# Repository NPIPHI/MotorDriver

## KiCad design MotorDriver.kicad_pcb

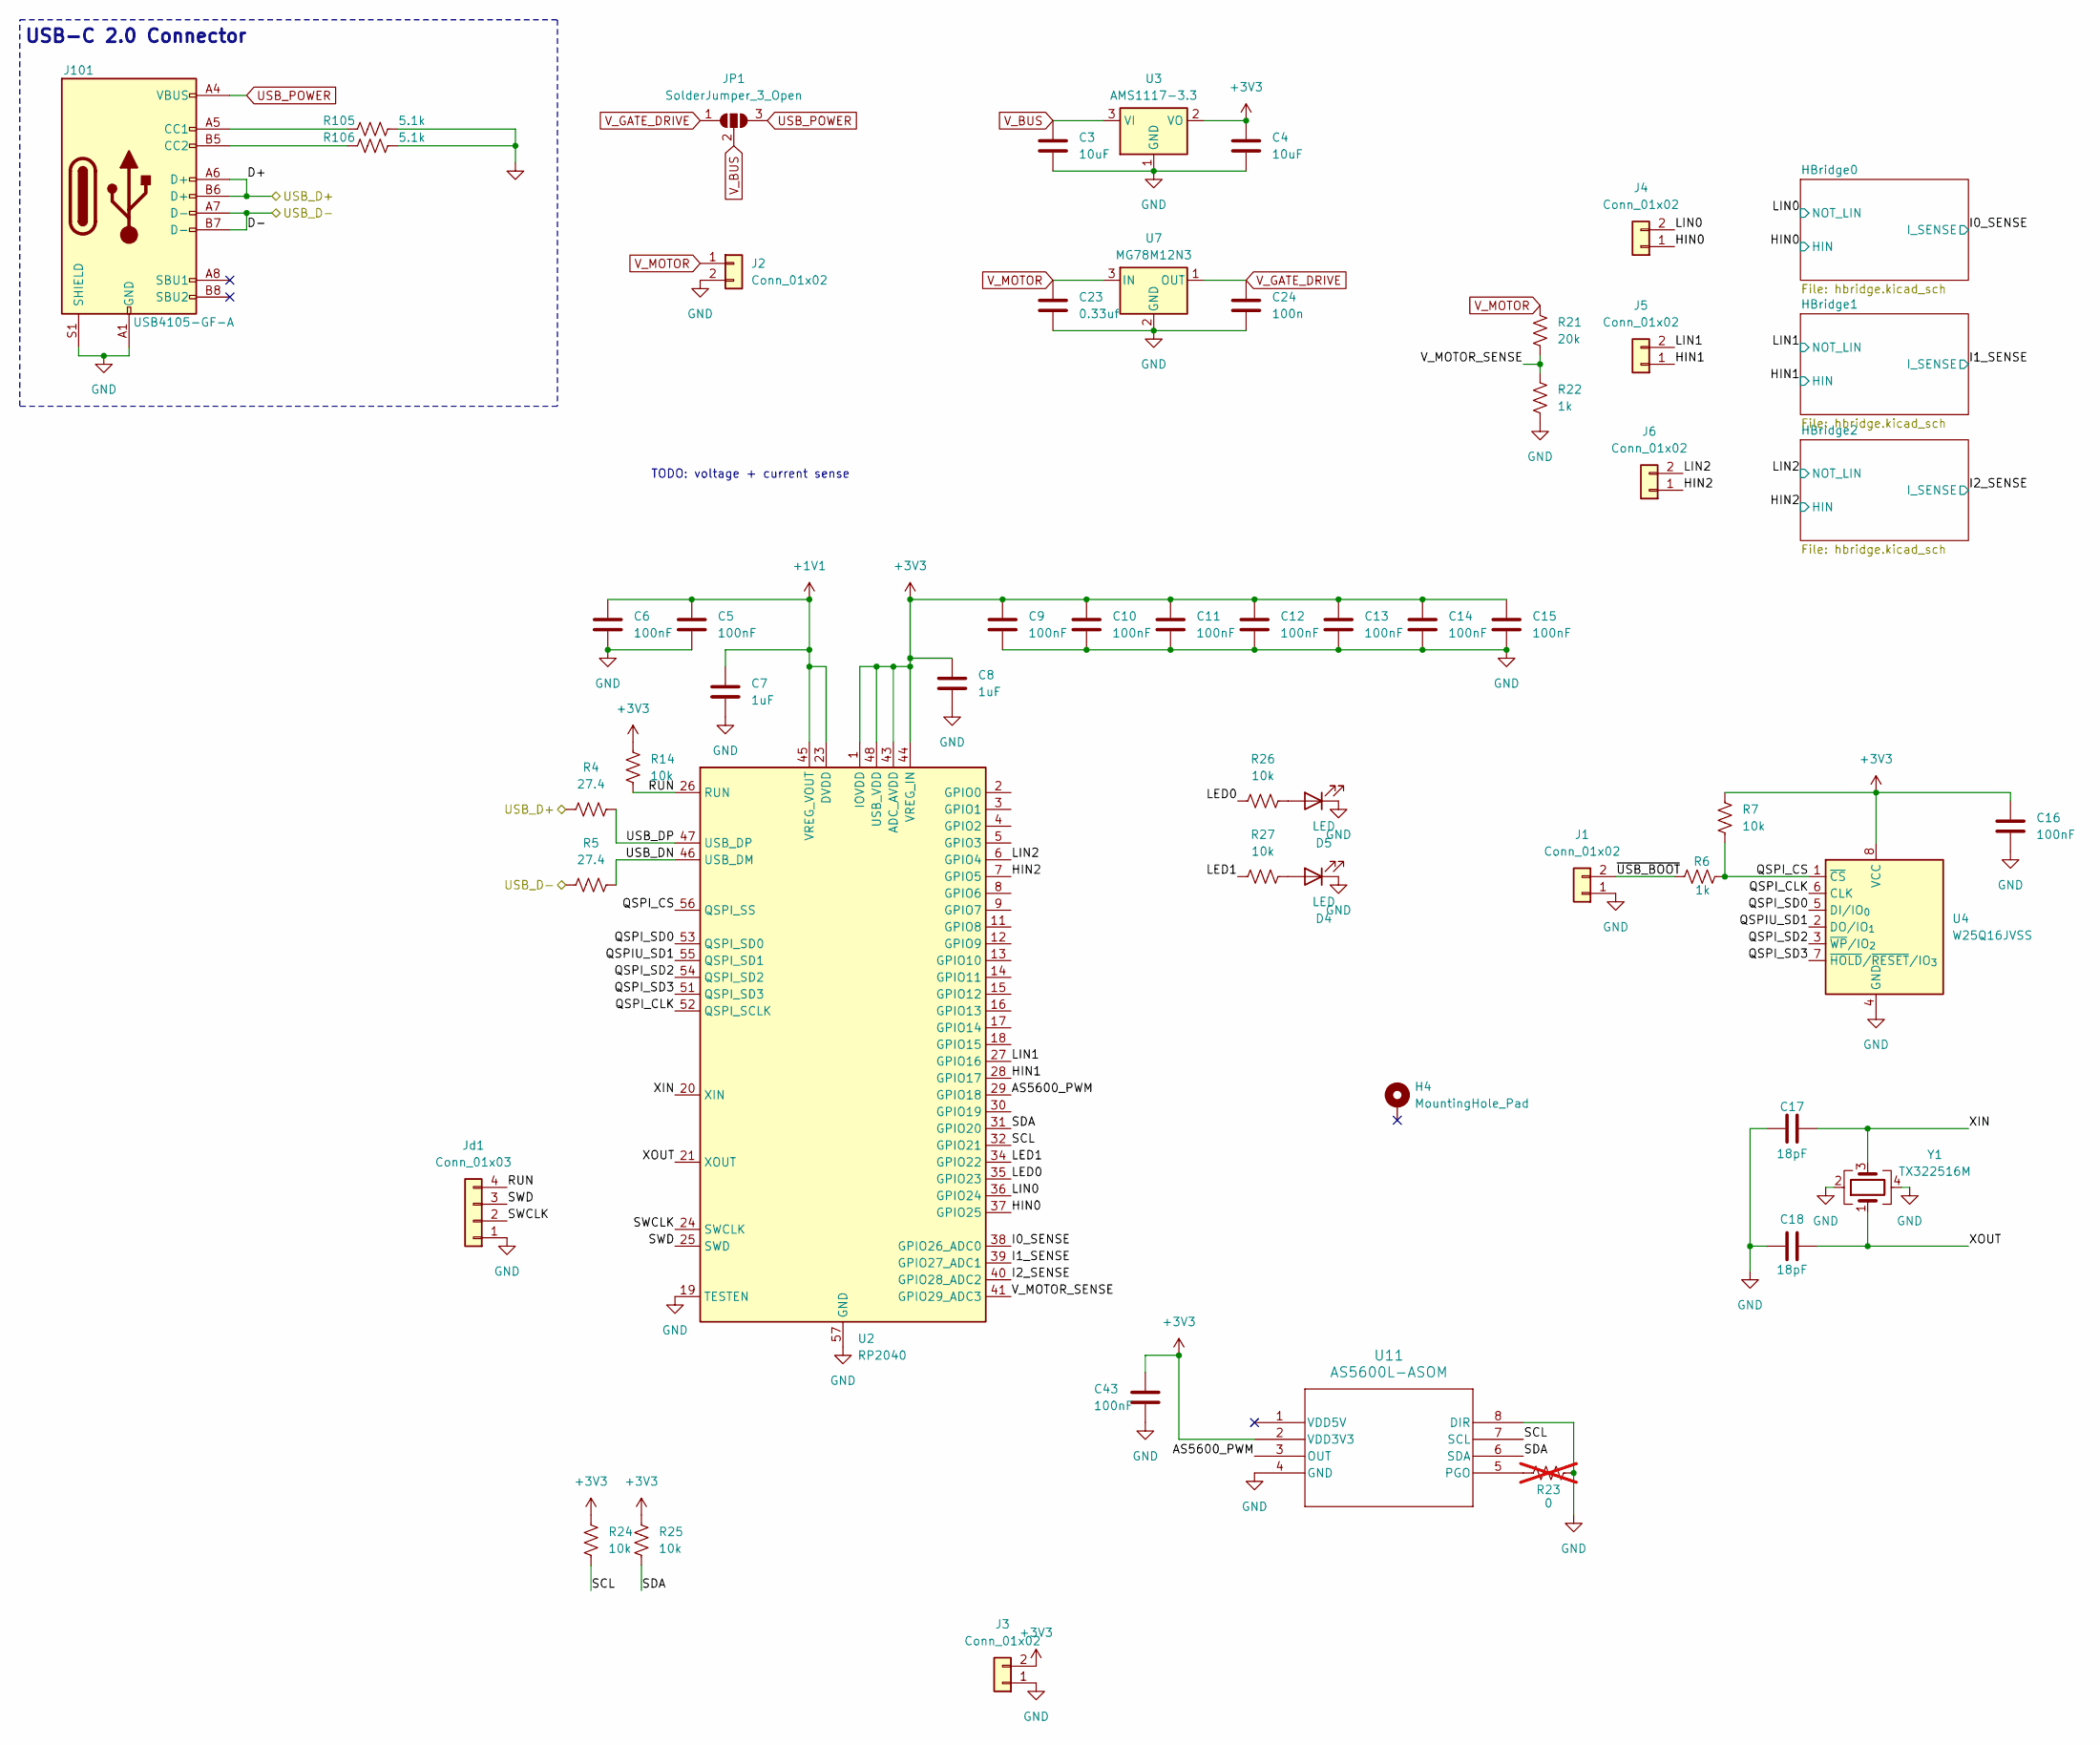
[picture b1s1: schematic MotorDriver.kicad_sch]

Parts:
C3, C4: 10uF; C_0603_1608Metric
C5, C6, C9, C10, C11, C12, C13, C14, C15, C16, C43: 100nF; C_0402_1005Metric
C7, C8: 1uF; C_0402_1005Metric
C17, C18: 18pF; C_0402_1005Metric
C23: 0.33uf; C_0603_1608Metric
C24: 100n; C_0603_1608Metric
D4, D5: LED; LED_0603_1608Metric
H4: MountingHole_Pad; MountingHole_3.2mm_M3_Pad_Via
J1, J3: Conn_01x02; PinHeader_1x02_P2.54mm_Vertical
J2: Conn_01x02; TerminalBlock_MaiXu_MX126-5.0-02P_1x02_P5.00mm
J4, J5, J6: Conn_01x02; PinHeader_1x02_P1.00mm_Vertical
J101: USB4105-GF-A; USB_C_Receptacle_GCT_USB4105-xx-A_16P_TopMnt_Horizontal
JP1: SolderJumper_3_Open; SolderJumper-3_P1.3mm_Open_RoundedPad1.0x1.5mm
Jd1: Conn_01x03; PinHeader_1x04_P2.54mm_Vertical
R4, R5: 27.4; R_0402_1005Metric
R6, R22: 1k; R_0402_1005Metric
R7, R14, R24, R25, R26, R27: 10k; R_0402_1005Metric
R21: 20k; R_0402_1005Metric
R23: 0; R_0402_1005Metric; not fitted
R105, R106: 5.1k; R_0603_1608Metric
U2: RP2040; QFN-56-1EP_7x7mm_P0.4mm_EP3.2x3.2mm
U3: AMS1117-3.3; SOT-223-3_TabPin2
U4: W25Q16JVSS; SOIC-8_5.3x5.3mm_P1.27mm
U7: MG78M12N3; SOT-89-3
U11: AS5600L-ASOM; AS5600L-ASOM_AMS
Y1: TX322516M; Crystal_SMD_3225-4Pin_3.2x2.5mm

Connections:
+1V1: C5.1, C6.1, C7.1, U2.23 (DVDD), U2.45 (VREG_VOUT), U2.50 (DVDD)
+3V3: C4.1, C8.1, C9.1, C10.1, C11.1, C12.1, C13.1, C14.1, C15.1, C16.1, C43.1, J3.2, R7.1, R14.2, R24.2, R25.2, U2.1 (IOVDD), U2.10 (IOVDD), U2.22 (IOVDD), U2.33 (IOVDD), U2.42 (IOVDD), U2.43 (ADC_AVDD), U2.44 (VREG_IN), U2.48 (USB_VDD), U2.49 (IOVDD), U3.2 (VO), U4.8 (VCC), U11.2 (VDD3V3); also elsewhere on the board
/AS5600_PWM: U2.29 (GPIO18), U11.3 (OUT)
/D+: J101.A6 (D+), J101.B6 (D+), R4.1
/D-: J101.A7 (D-), J101.B7 (D-), R5.1
/HIN0: J4.1, U2.37 (GPIO25); also elsewhere on the board
/HIN1: J5.1, U2.28 (GPIO17); also elsewhere on the board
/HIN2: J6.1, U2.7 (GPIO5); also elsewhere on the board
/I0_SENSE: U2.38 (GPIO26_ADC0); also elsewhere on the board
/I1_SENSE: U2.39 (GPIO27_ADC1); also elsewhere on the board
/I2_SENSE: U2.40 (GPIO28_ADC2); also elsewhere on the board
/LED0: R26.2, U2.35 (GPIO23)
/LED1: R27.2, U2.34 (GPIO22)
/LIN0: J4.2, U2.36 (GPIO24); also elsewhere on the board
/LIN1: J5.2, U2.27 (GPIO16); also elsewhere on the board
/LIN2: J6.2, U2.6 (GPIO4); also elsewhere on the board
/QSPIU_SD1: U2.55 (QSPI_SD1), U4.2 (DO/IO_{1})
/QSPI_CLK: U2.52 (QSPI_SCLK), U4.6 (CLK)
/QSPI_CS: R6.1, R7.2, U2.56 (QSPI_SS), U4.1 (~CS)
/QSPI_SD0: U2.53 (QSPI_SD0), U4.5 (DI/IO_{0})
/QSPI_SD2: U2.54 (QSPI_SD2), U4.3 (~WP/IO_{2})
/QSPI_SD3: U2.51 (QSPI_SD3), U4.7 (~HOLD/~RESET/IO_{3})
/RUN: Jd1.4, R14.1, U2.26 (RUN)
/SCL: R24.1, U2.32 (GPIO21), U11.7 (SCL)
/SDA: R25.1, U2.31 (GPIO20), U11.6 (SDA)
/SWCLK: Jd1.2, U2.24 (SWCLK)
/SWD: Jd1.3, U2.25 (SWD)
/USB_DN: R5.2, U2.46 (USB_DM)
/USB_DP: R4.2, U2.47 (USB_DP)
/V_MOTOR_SENSE: R21.1, R22.2, U2.41 (GPIO29_ADC3)
/XIN: C17.1, U2.20 (XIN), Y1.3
/XOUT: C18.2, U2.21 (XOUT), Y1.1
/~USB_BOOT: J1.2, R6.2
GND: C3.2, C4.2, C5.2, C6.2, C7.2, C8.2, C9.2, C10.2, C11.2, C12.2, C13.2, C14.2, C15.2, C16.2, C17.2, C18.1, C23.2, C24.2, C43.2, D4.1 (K), D5.1 (K), J1.1, J2.2, J3.1, J101.A1 (GND), J101.A12 (GND), J101.B1 (GND), J101.B12 (GND), J101.S1 (SHIELD), Jd1.1, R22.1, R23.2, R105.1, R106.1, U2.19 (TESTEN), U2.57 (GND), U3.1 (GND), U4.4 (GND), U7.2 (GND), U11.4 (GND), U11.8 (DIR), Y1.2, Y1.4; also elsewhere on the board
unnamed: D4.2 (A), R27.1
unnamed: D5.2 (A), R26.1
unnamed: J101.A5 (CC1), R105.2
unnamed: J101.B5 (CC2), R106.2
unnamed: R23.1, U11.5 (PGO)
USB_POWER: J101.A4 (VBUS), J101.A9 (VBUS), J101.B4 (VBUS), J101.B9 (VBUS), JP1.3 (B)
V_BUS: C3.1, JP1.2 (C), U3.3 (VI)
V_GATE_DRIVE: C24.1, JP1.1 (A), U7.1 (OUT); also elsewhere on the board
V_MOTOR: C23.1, J2.1, R21.2, U7.3 (IN); also elsewhere on the board

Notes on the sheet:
TODO: voltage + current sense
USB-C 2.0 Connector

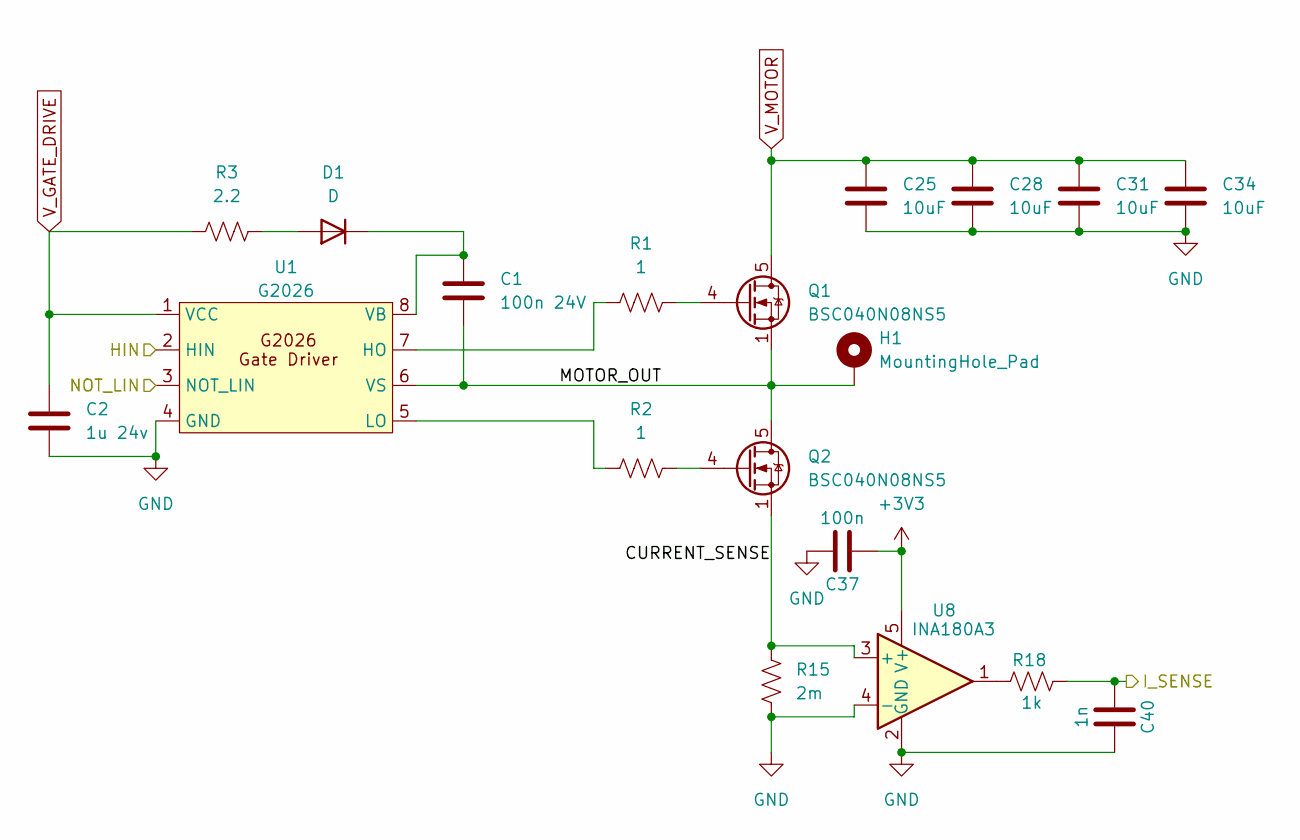
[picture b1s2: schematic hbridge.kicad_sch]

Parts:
C1: 100n 24V; C_0402_1005Metric
C2: 1u 24v; C_0402_1005Metric
C25, C28, C31, C34: 10uF; C_1206_3216Metric
C37: 100n; C_0402_1005Metric
C40: 1n; C_0402_1005Metric
D1: D; D_SOD-123F
H1: MountingHole_Pad; MountingHole_5.3mm_M5_Pad_Via
Q1, Q2: BSC040N08NS5; TDSON-8-1
R1, R2: 1; R_0402_1005Metric
R3: 2.2; R_0402_1005Metric
R15: 2m; R_1206_3216Metric
R18: 1k; R_0402_1005Metric
U1: G2026; SOIC-8_3.9x4.9mm_P1.27mm
U8: INA180A3; SOT-23-5

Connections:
+3V3: C37.2, U8.5 (V+); also elsewhere on the board
/HBridge0/CURRENT_SENSE: Q2.1 (S), Q2.2 (S), Q2.3 (S), R15.1, U8.3 (+)
/HBridge0/MOTOR_OUT: C1.2, H1.1, Q1.1 (S), Q1.2 (S), Q1.3 (S), Q2.5 (D), U1.6 (VS)
/HIN0: U1.2 (HIN); also elsewhere on the board
/I0_SENSE: C40.2, R18.2; also elsewhere on the board
/LIN0: U1.3 (NOT_LIN); also elsewhere on the board
GND: C2.2, C25.2, C28.2, C31.2, C34.2, C37.1, C40.1, R15.2, U1.4 (GND), U8.2 (GND), U8.4 (-); also elsewhere on the board
unnamed: D1.2 (A), R3.2
unnamed: C1.1, D1.1 (K), U1.8 (VB)
unnamed: Q1.4 (G), R1.2
unnamed: Q2.4 (G), R2.2
unnamed: R18.1, U8.1
unnamed: R1.1, U1.7 (HO)
unnamed: R2.1, U1.5 (LO)
V_GATE_DRIVE: C2.1, R3.1, U1.1 (VCC); also elsewhere on the board
V_MOTOR: C25.1, C28.1, C31.1, C34.1, Q1.5 (D); also elsewhere on the board

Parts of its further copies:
C19, C21: 1u 24v; C_0402_1005Metric
C20, C22: 100n 24V; C_0402_1005Metric
C26, C27, C29, C30, C32, C33, C35, C36: 10uF; C_1206_3216Metric
C38, C39: 100n; C_0402_1005Metric
C41, C42: 1n; C_0402_1005Metric
D2, D3: D; D_SOD-123F
H2, H3: MountingHole_Pad; MountingHole_5.3mm_M5_Pad_Via
Q3, Q4, Q5, Q6: BSC040N08NS5; TDSON-8-1
R8, R11: 2.2; R_0402_1005Metric
R9, R10, R12, R13: 1; R_0402_1005Metric
R16, R17: 2m; R_1206_3216Metric
R19, R20: 1k; R_0402_1005Metric
U5, U6: G2026; SOIC-8_3.9x4.9mm_P1.27mm
U9, U10: INA180A3; SOT-23-5

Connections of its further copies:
+3V3: C38.2, C39.2, U9.5 (V+), U10.5 (V+); also elsewhere on the board
/HBridge1/CURRENT_SENSE: Q4.1 (S), Q4.2 (S), Q4.3 (S), R16.1, U9.3 (+)
/HBridge1/MOTOR_OUT: C20.2, H2.1, Q3.1 (S), Q3.2 (S), Q3.3 (S), Q4.5 (D), U5.6 (VS)
/HBridge2/CURRENT_SENSE: Q6.1 (S), Q6.2 (S), Q6.3 (S), R17.1, U10.3 (+)
/HBridge2/MOTOR_OUT: C22.2, H3.1, Q5.1 (S), Q5.2 (S), Q5.3 (S), Q6.5 (D), U6.6 (VS)
/HIN1: U5.2 (HIN); also elsewhere on the board
/HIN2: U6.2 (HIN); also elsewhere on the board
/I1_SENSE: C41.2, R19.2; also elsewhere on the board
/I2_SENSE: C42.2, R20.2; also elsewhere on the board
/LIN1: U5.3 (NOT_LIN); also elsewhere on the board
/LIN2: U6.3 (NOT_LIN); also elsewhere on the board
GND: C19.2, C21.2, C26.2, C27.2, C29.2, C30.2, C32.2, C33.2, C35.2, C36.2, C38.1, C39.1, C41.1, C42.1, R16.2, R17.2, U5.4 (GND), U6.4 (GND), U9.2 (GND), U9.4 (-), U10.2 (GND), U10.4 (-); also elsewhere on the board
unnamed: D2.2 (A), R8.2
unnamed: C20.1, D2.1 (K), U5.8 (VB)
unnamed: D3.2 (A), R11.2
unnamed: C22.1, D3.1 (K), U6.8 (VB)
unnamed: Q3.4 (G), R9.2
unnamed: Q4.4 (G), R10.2
unnamed: Q5.4 (G), R12.2
unnamed: Q6.4 (G), R13.2
unnamed: R19.1, U9.1
unnamed: R20.1, U10.1
unnamed: R9.1, U5.7 (HO)
unnamed: R10.1, U5.5 (LO)
unnamed: R12.1, U6.7 (HO)
unnamed: R13.1, U6.5 (LO)
V_GATE_DRIVE: C19.1, C21.1, R8.1, R11.1, U5.1 (VCC), U6.1 (VCC); also elsewhere on the board
V_MOTOR: C26.1, C27.1, C29.1, C30.1, C32.1, C33.1, C35.1, C36.1, Q3.5 (D), Q5.5 (D); also elsewhere on the board

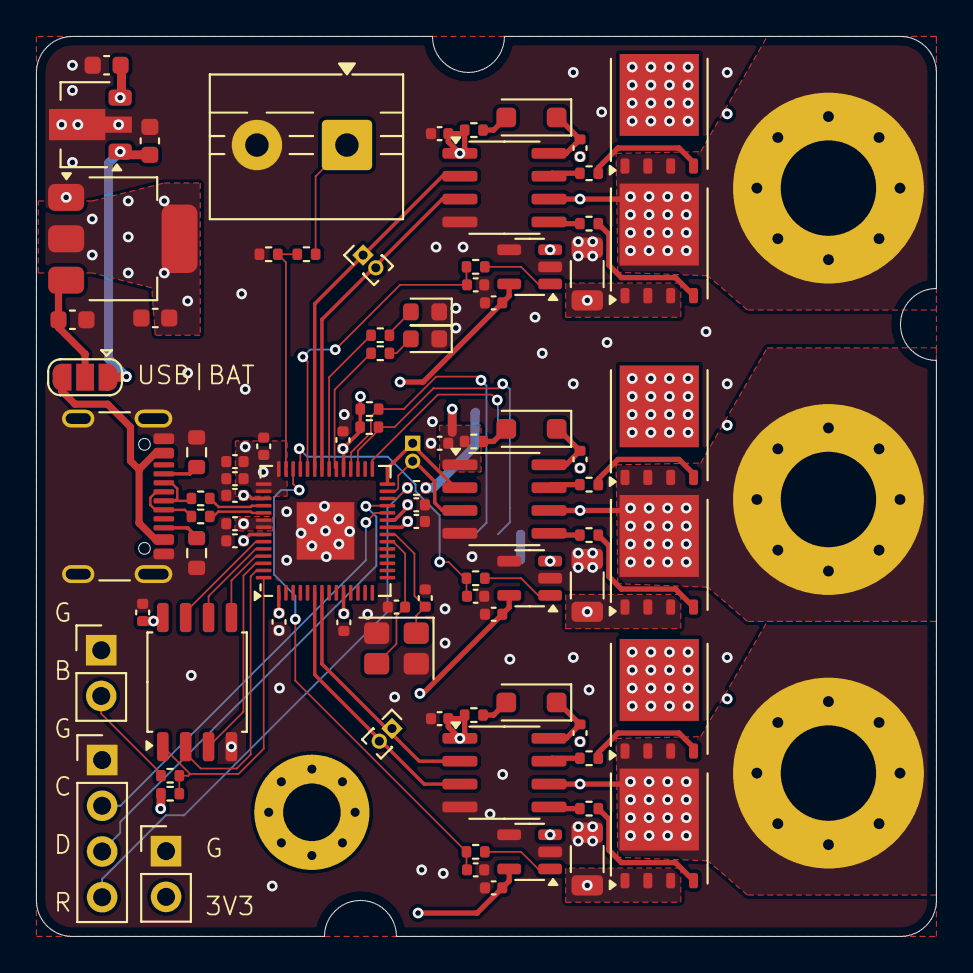
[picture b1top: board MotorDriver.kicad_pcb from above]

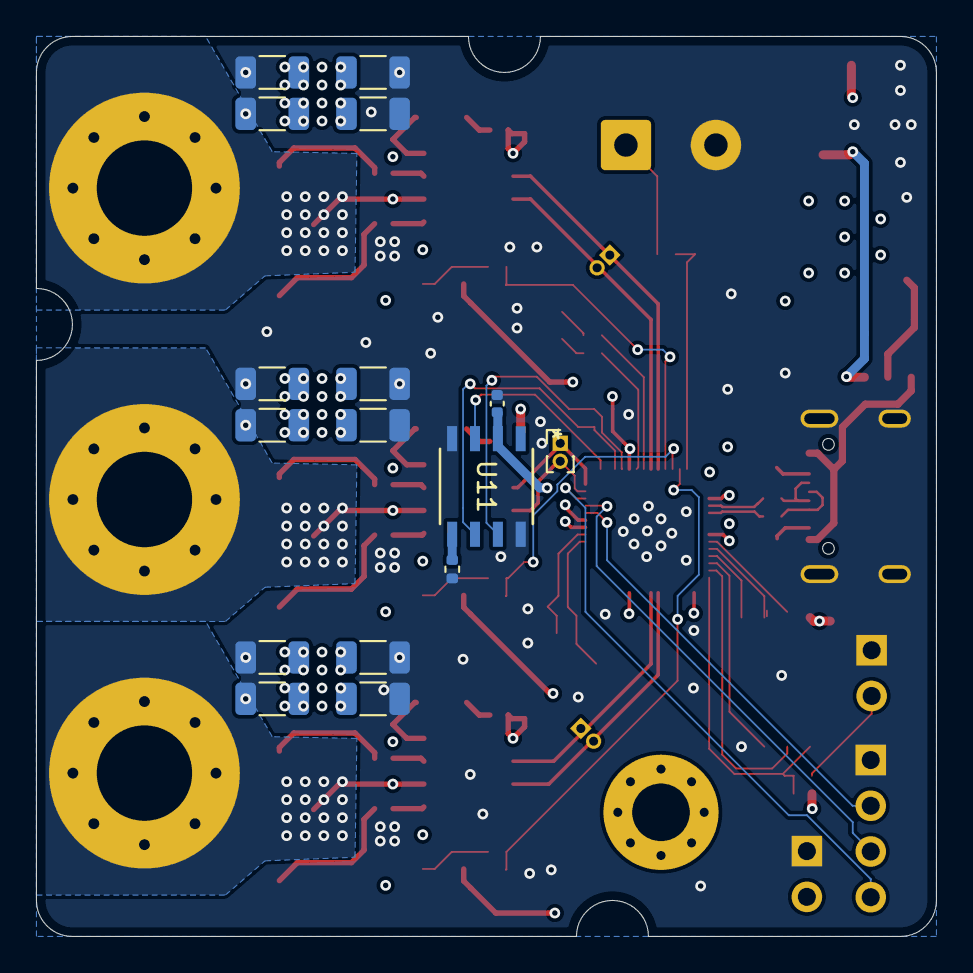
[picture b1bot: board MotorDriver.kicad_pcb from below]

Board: 8 copper layers, 50.0 x 50.0 mm, 108 parts (16 on the bottom side), 70 nets.

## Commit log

2025-12-31 rev 1
2026-01-01 populate 10k
